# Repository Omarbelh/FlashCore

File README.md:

<div align="center">

# ⚡ FlashCore V1

### Hybrid USB-C Memory Programmer
**Powered by CH341A + ESP32-S3**

*A custom hardware programmer designed for learning, development, and future standalone memory programming.*

---

</div>

---

# 📖 About

FlashCore V1 is an open-source hardware project that combines the reliability of the **CH341A USB programmer** with the flexibility of an **ESP32-S3**.

The goal is to create a modern memory programmer that can operate both from a computer and, in future versions, as a standalone device with its own graphical user interface.

This project is also a personal journey to improve my skills in:

- PCB Design
- Embedded Systems
- Hardware Development
- KiCad
- ESP32
- USB Devices
- Memory Technologies

---

# ✨ Current Features

- ✅ USB-C Interface
- ✅ CH341A Programming Circuit
- ✅ ESP32-S3 Controller
- ✅ 320×240 TFT Display
- ✅ Standalone Buttons
- ✅ Status LEDs
- ✅ Buzzer
- ✅ Hybrid Hardware Architecture

---

# 🖼️ Project Images

## PCB Layout

---

## Main Schematic

---

## ESP32 Standalone Controller

---

# 🧩 Hardware

| Component | Description |
|-----------|-------------|
| CH341A | USB Memory Programmer |
| ESP32-S3-WROOM-1 | Standalone Controller |
| AP2112K | 3.3V LDO Regulator |
| USB-C | Power & Data |
| TFT Display | User Interface |
| Push Buttons | Read / Write / Erase / Menu |
| Status LEDs | Power & Status |
| Buzzer | Audio Feedback |

---

# 🚀 Project Status

| Stage | Status |
|--------|--------|
| Concept | ✅ Completed |
| Schematic | ✅ Completed |
| PCB Layout | 🚧 In Progress |
| Prototype | ⏳ Planned |
| Firmware | ⏳ Planned |
| Standalone Mode | ⏳ Planned |

---

# 🛣️ Roadmap

## FlashCore V1

- [x] Schematic Design
- [x] ESP32 Integration
- [x] USB-C Interface
- [ ] PCB Routing
- [ ] Prototype Assembly
- [ ] Hardware Testing

## FlashCore V2

- [ ] 1.8V Support
- [ ] ZIF Socket
- [ ] Automatic Voltage Selection
- [ ] Better User Interface

## FlashCore V3

- [ ] EEPROM Support
- [ ] EPROM Support
- [ ] NAND Flash
- [ ] NOR Flash
- [ ] Standalone Firmware Update

---

# 📂 Repository Structure

```text
FlashCore/
│
├── Hardware/
│   ├── KiCad/
│   ├── PDF/
│   └── Images/
│
├── Firmware/
│
├── Documentation/
│
├── README.md
└── LICENSE
```

---

# 🤝 Contributing

Contributions, suggestions, and ideas are always welcome.

If you find an issue or have an idea for improving FlashCore, feel free to open an Issue or submit a Pull Request.

---

# 📜 License

This project is released under the **MIT License**.

---

<div align="center">

### Designed and Developed by

# Omar Belh

⭐ If you like this project, consider giving it a star!

</div>

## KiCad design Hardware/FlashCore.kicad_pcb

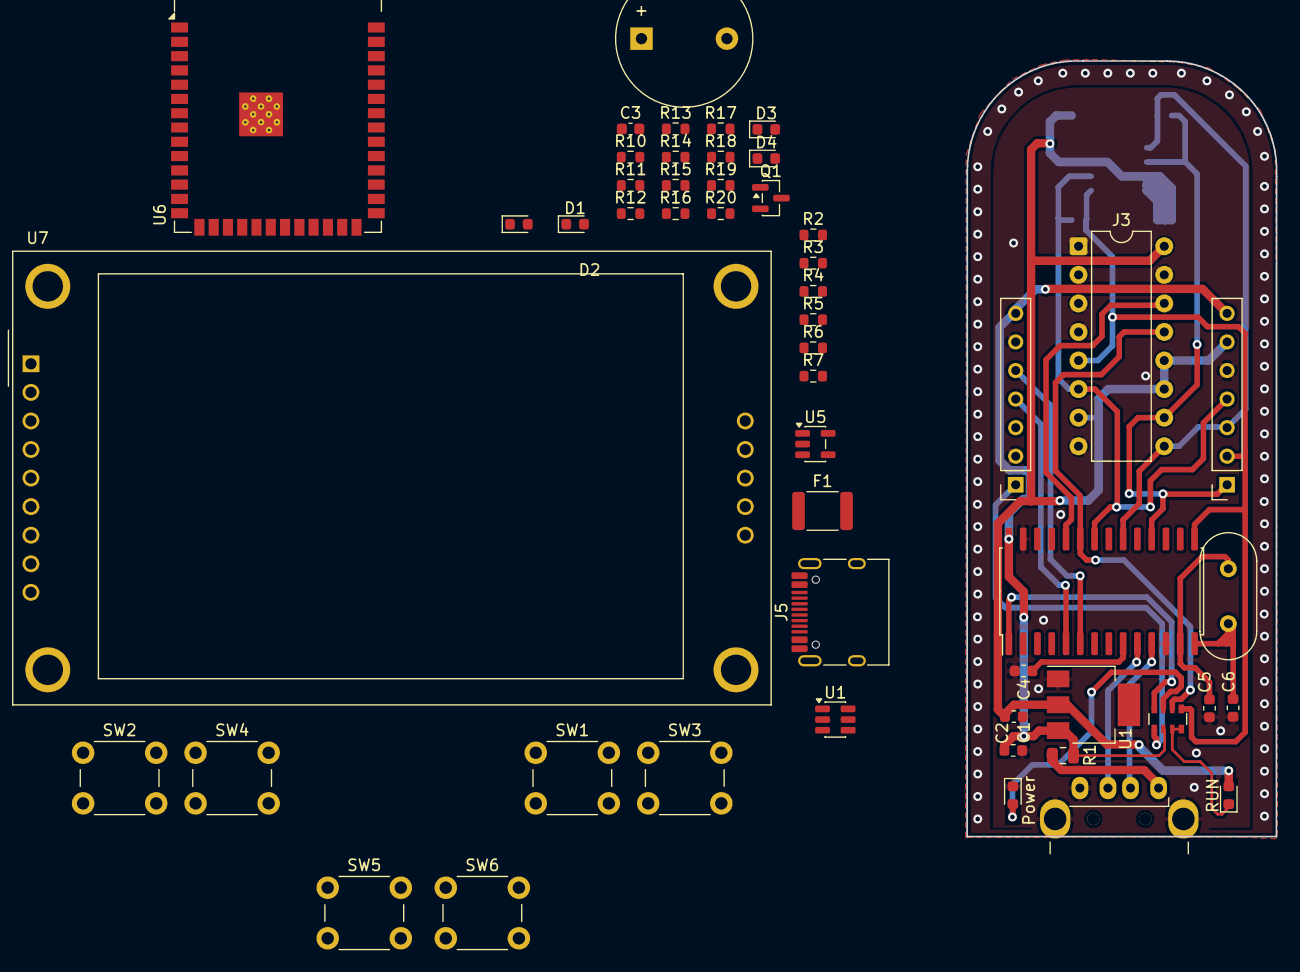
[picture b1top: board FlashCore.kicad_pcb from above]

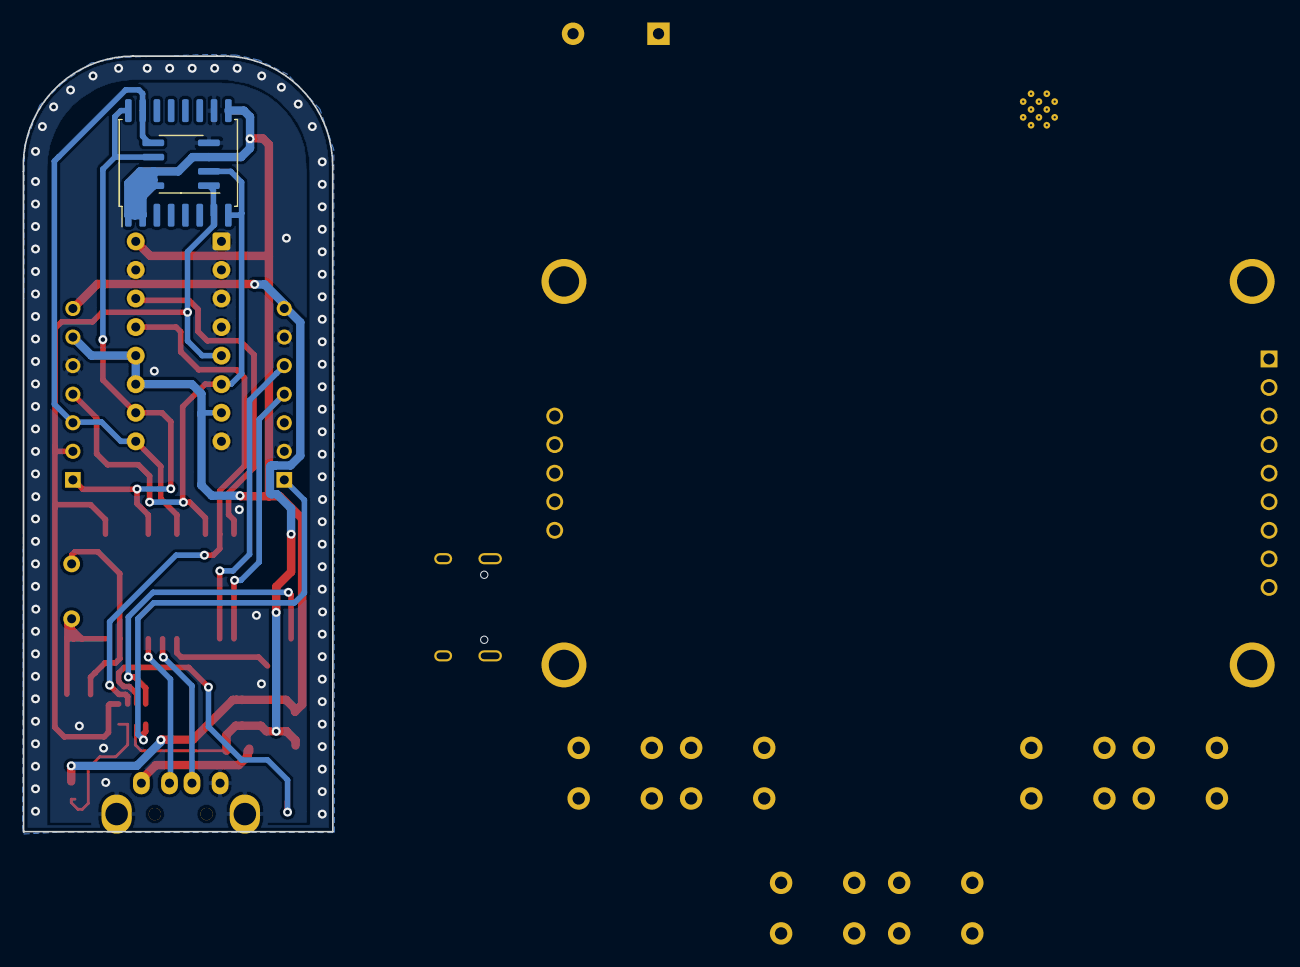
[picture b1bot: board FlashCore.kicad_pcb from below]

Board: 2 copper layers, 27.5 x 69.0 mm, 54 parts (2 on the bottom side), 53 nets.

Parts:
BZ1: Buzzer; Buzzer_12x9.5RM7.6
C1, C2: 104; C_0603_1608Metric
C3: 1µF; C_0603_1608Metric
C4: 472; C_0603_1608Metric
C5, C6: 20p; C_0603_1608Metric
D1, D1#2: Power; LED_0603_1608Metric
D2: RUN; LED_0603_1608Metric
D2#2: Run; LED_0603_1608Metric
D3, D4: LED; LED_0603_1608Metric
F1: Polyfuse; Fuse_1812_4532Metric
J1: USB_A; USB_A_MALE_Generic
J2, J4: Conn_01x07; PinSocket_1x07_P2.54mm_Vertical
J3: ZIF-16; DIP-16_W7.62mm
J5: USB_C_Receptacle_USB2.0; USB_C_Receptacle_HRO_TYPE-C-31-M-12
Q1: S8050; SOT-23
R1: 0R; R_0805_2012Metric
R2, R3: 5.1kΩ; R_0603_1608Metric
R4, R5: 22Ω; R_0603_1608Metric
R6: -10kΩ; R_0603_1608Metric
R7, R10, R11, R12, R13, R17, R18: 10kΩ; R_0603_1608Metric
R14, R15: 330Ω; R_0603_1608Metric
R16: 1KΩ; R_0603_1608Metric
R19, R20: 100Ω; R_0603_1608Metric
RN1: 222; R_Array_Convex_4x0603
SW1: ERASE; SW_PUSH_6mm
SW2: READ; SW_PUSH_6mm
SW3: MENU; SW_PUSH_6mm
SW4: WRITE; SW_PUSH_6mm
SW5: BOOT; SW_PUSH_6mm
SW6: RESET; SW_PUSH_6mm
U1: AMS1117-3.3; SOT-223-3_TabPin2
U1#2: USBLC6-2SC6; SOT-23-6
U2: CH341a; SOIC-28W_7.5x17.9mm_P1.27mm
U3: SPI FLASH; SOIC-16W_7.5x10.3mm_P1.27mm
U4: I2C EEPROM; SOIC-8_3.9x4.9mm_P1.27mm
U5: AP2112K-3.3; SOT-23-5
U6: ESP32-S3-WROOM-1
U7: TFT-MI2120; CR2013-MI2120
Y1: 12M; Crystal_HC49-U_Vertical

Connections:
/1: J2.1, RN1.5 (R4.2)
/3V3: C2.1, D2.2, D2#2.2 (A), J3.7, J3.11, J3.12, J3.16, J4.6, R6.2, R7.1, U1.2, U3.2 (VCC), U4.3 (E2), U4.7 (~WC), U4.8 (VCC), U5.5 (VOUT)
/5V: C1.1, F1.1, J2.7, J4.7, R1.1, RN1.6 (R3.2), U1.3, U1#2.5 (VBUS), U2.28 (VCC), U5.1 (VIN), U5.3 (EN)
/CLK: J3.10, J4.1, U2.18 (~DCD/D3/DCK), U3.16 (SCK), U4.6 (SCL)
/CS: J3.5, J4.2, RN1.1 (R1.1), U2.15 (~CTS/D0/CS0), U3.7 (~CE), U4.1 (E0)
/ESP32_Standalone/3V3: BZ1.1 (+), R10.1, R11.1, R12.1, R13.1, R17.1, R18.1, U6.2 (3V3), U7.1 (VCC), U7.8 (LED)
/MISO: J3.6, J4.4, U2.22 (~SLP/D7/DIN), U3.8 (SO/IO1), U4.2 (E1)
/MOSI: J3.9, J4.3, U2.20 (~DTR/D5/DOUT), U3.15 (SI/IO0), U4.5 (SDA)
/RXD: J2.5, U2.6 (RXD/PEMP/USERDEF)
/SCL: J3.14, U2.24 (SCL)
/SDA: J3.13, RN1.2 (R2.1), U2.23 (SDA)
/TXD: J2.4, U2.5 (TXD/~ERR/USERDEF)
Earth: D1.1, J1.4, J1.5, U1.1
GND: C1.2, C2.2, C3.2, C4.2, C5.2, C6.2, D1#2.1 (K), D3.1 (K), D4.1 (K), J2.2, J2.6, J3.1, J3.2, J3.3, J3.4, J3.8, J3.15, J4.5, J5.A1 (GND), J5.A12 (GND), J5.B1 (GND), J5.B12 (GND), J5.SH (SHIELD), Q1.1 (E), R2.2, R3.2, SW1.1, SW2.1, SW3.2, SW4.2, SW5.2, SW6.2, U1#2.2 (GND), U2.12 (GND), U2.27 (~TEN/BUSY/WAIT), U3.10 (GND), U4.4 (VSS), U5.2 (GND), U6.1 (GND), U6.40 (GND), U6.41 (GND), U7.2 (GND)
unnamed: BZ1.2 (-), Q1.3 (C)
unnamed: D1#2.2 (A), RN1.3 (R3.1)
unnamed: D2#2.1 (K), RN1.7 (R2.2), RN1.8 (R1.2)
unnamed: D3.2 (A), R14.2
unnamed: D4.2 (A), R15.2
unnamed: F1.2, J5.A4 (VBUS), J5.A9 (VBUS), J5.B4 (VBUS), J5.B9 (VBUS)
unnamed: J1.1, R1.2
unnamed: J5.A5 (CC1), R3.1
unnamed: J5.B5 (CC2), R2.1
unnamed: J5.A6 (D+), J5.B6 (D+)
unnamed: J5.A7 (D-), J5.B7 (D-)
unnamed: Q1.2 (B), R16.1
unnamed: R4.2, U1#2.1 (I/O1), U1#2.6 (I/O1)
unnamed: R5.2, U1#2.3 (I/O2), U1#2.4 (I/O2)
unnamed: RN1.4 (R4.1), U2.1 (~ACT)
unnamed: R5.1, U2.10 (UD+)
unnamed: R4.1, U2.11 (UD-)
unnamed: C4.1, U2.9 (V3)
unnamed: C5.1, U2.13 (XI), Y1.1
unnamed: C6.1, U2.14 (XO), Y1.2
unnamed: R6.1, U3.1 (~HOLD/IO3)
unnamed: R7.2, U3.9 (~WP/IO2)
unnamed: C3.1, R17.2, SW6.1, U6.3 (EN)
unnamed: R18.2, SW5.1, U6.27 (IO0)
unnamed: R10.2, SW2.2, U6.4 (IO4)
unnamed: R11.2, SW4.1, U6.5 (IO5)
unnamed: R12.2, SW1.2, U6.6 (IO6)
unnamed: R13.2, SW3.1, U6.7 (IO7)
unnamed: U6.19 (IO11), U7.6 (MOSI), U7.11 (SD_MOSI)
unnamed: U6.20 (IO12), U7.7 (SCK), U7.13 (SD_SCK)
unnamed: R20.2, U6.21 (IO13)
unnamed: U6.8 (IO15), U7.3 (~CS), U7.10 (SD_CS)
unnamed: U6.9 (IO16), U7.5 (D/~C)
unnamed: U6.10 (IO17), U7.4 (RESET)
unnamed: R15.1, U6.33 (IO40)
unnamed: R14.1, U6.34 (IO41)
unnamed: R16.2, U6.35 (IO42)
unnamed: R19.2, R20.1, U7.9 (MISO)
unnamed: R19.1, U7.12 (SD_MISO)
